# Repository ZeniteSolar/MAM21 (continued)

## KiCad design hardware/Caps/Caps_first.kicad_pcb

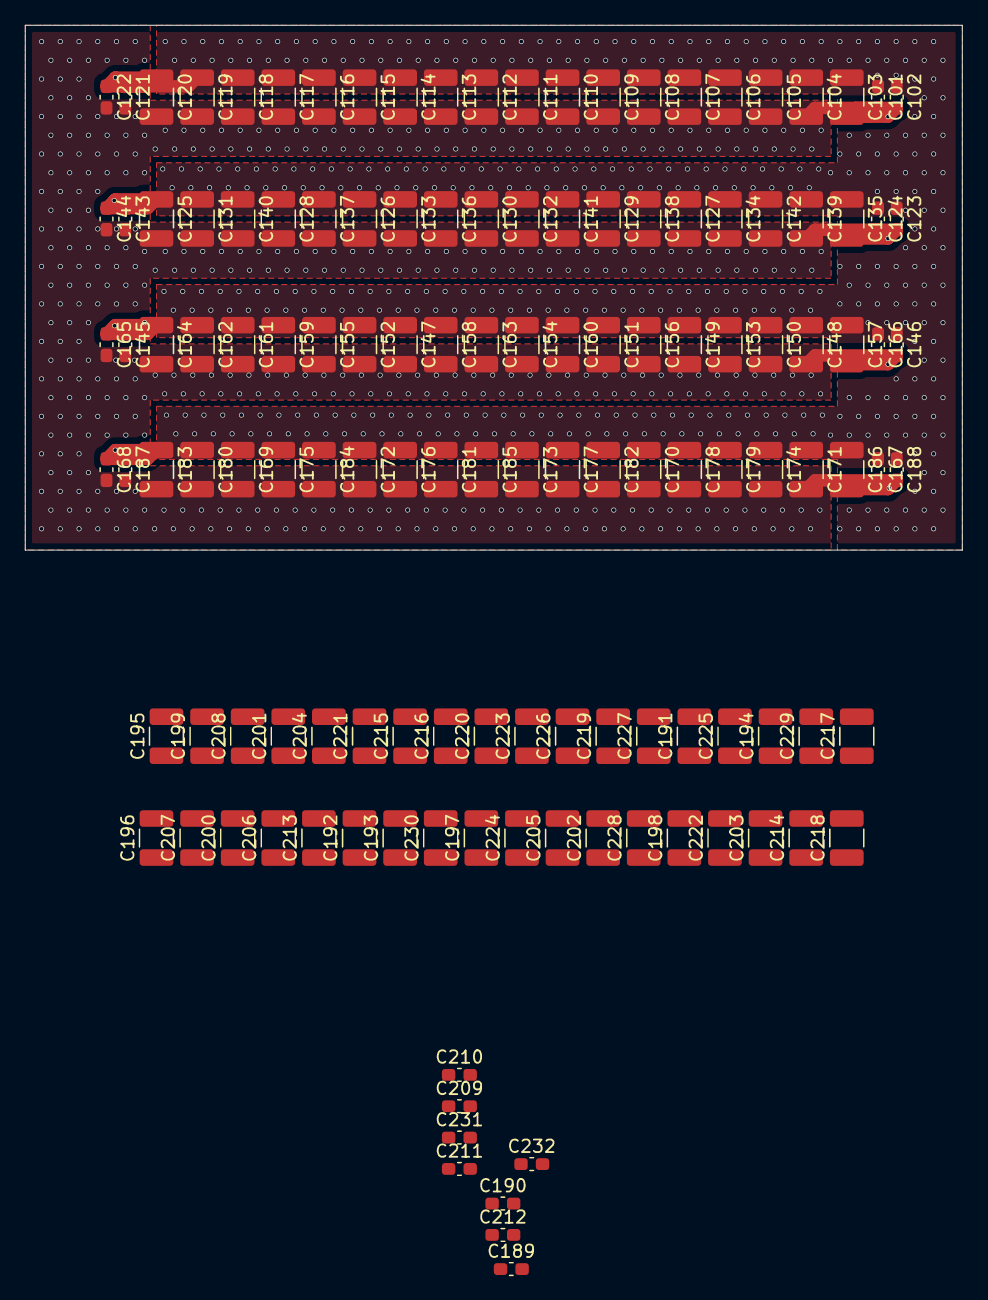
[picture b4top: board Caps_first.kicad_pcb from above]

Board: 2 copper layers, 75.0 x 42.0 mm, 132 parts (0 on the bottom side), 2 nets.

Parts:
C101, C102, C121, C122, C123, C124, C143, C144, C145, C146, C165, C166, C167, C168, C187, C188, C189, C190, C209, C210, C211, C212, C231, C232: 100n 100V X7; C_0603_1608Metric_Pad1.08x0.95mm_HandSolder
C103, C104, C105, C106, C107, C108, C109, C110, C111, C112, C113, C114, C115, C116, C117, C118, C119, C120, C125, C126, C127, C128, C129, C130, C131, C132, C133, C134, C135, C136, C137, C138, C139, C140, C141, C142, C147, C148, C149, C150, C151, C152, C153, C154, C155, C156, C157, C158, C159, C160, C161, C162, C163, C164, C169, C170, C171, C172, C173, C174, C175, C176, C177, C178, C179, C180, C181, C182, C183, C184, C185, C186, C191, C192, C193, C194, C195, C196, C197, C198, C199, C200, C201, C202, C203, C204, C205, C206, C207, C208, C213, C214, C215, C216, C217, C218, C219, C220, C221, C222, C223, C224, C225, C226, C227, C228, C229, C230: 4.7u 100V X7; C_1210_3225Metric_Pad1.33x2.70mm_HandSolder

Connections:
+BATT: C101.1, C102.1, C103.1, C104.1, C105.1, C106.1, C107.1, C108.1, C109.1, C110.1, C111.1, C112.1, C113.1, C114.1, C115.1, C116.1, C117.1, C118.1, C119.1, C120.1, C121.1, C122.1, C123.1, C124.1, C125.1, C126.1, C127.1, C128.1, C129.1, C130.1, C131.1, C132.1, C133.1, C134.1, C135.1, C136.1, C137.1, C138.1, C139.1, C140.1, C141.1, C142.1, C143.1, C144.1, C145.1, C146.1, C147.1, C148.1, C149.1, C150.1, C151.1, C152.1, C153.1, C154.1, C155.1, C156.1, C157.1, C158.1, C159.1, C160.1, C161.1, C162.1, C163.1, C164.1, C165.1, C166.1, C167.1, C168.1, C169.1, C170.1, C171.1, C172.1, C173.1, C174.1, C175.1, C176.1, C177.1, C178.1, C179.1, C180.1, C181.1, C182.1, C183.1, C184.1, C185.1, C186.1, C187.1, C188.1, C189.1, C190.1, C191.1, C192.1, C193.1, C194.1, C195.1, C196.1, C197.1, C198.1, C199.1, C200.1, C201.1, C202.1, C203.1, C204.1, C205.1, C206.1, C207.1, C208.1, C209.1, C210.1, C211.1, C212.1, C213.1, C214.1, C215.1, C216.1, C217.1, C218.1, C219.1, C220.1, C221.1, C222.1, C223.1, C224.1, C225.1, C226.1, C227.1, C228.1, C229.1, C230.1, C231.1, C232.1
-BATT: C101.2, C102.2, C103.2, C104.2, C105.2, C106.2, C107.2, C108.2, C109.2, C110.2, C111.2, C112.2, C113.2, C114.2, C115.2, C116.2, C117.2, C118.2, C119.2, C120.2, C121.2, C122.2, C123.2, C124.2, C125.2, C126.2, C127.2, C128.2, C129.2, C130.2, C131.2, C132.2, C133.2, C134.2, C135.2, C136.2, C137.2, C138.2, C139.2, C140.2, C141.2, C142.2, C143.2, C144.2, C145.2, C146.2, C147.2, C148.2, C149.2, C150.2, C151.2, C152.2, C153.2, C154.2, C155.2, C156.2, C157.2, C158.2, C159.2, C160.2, C161.2, C162.2, C163.2, C164.2, C165.2, C166.2, C167.2, C168.2, C169.2, C170.2, C171.2, C172.2, C173.2, C174.2, C175.2, C176.2, C177.2, C178.2, C179.2, C180.2, C181.2, C182.2, C183.2, C184.2, C185.2, C186.2, C187.2, C188.2, C189.2, C190.2, C191.2, C192.2, C193.2, C194.2, C195.2, C196.2, C197.2, C198.2, C199.2, C200.2, C201.2, C202.2, C203.2, C204.2, C205.2, C206.2, C207.2, C208.2, C209.2, C210.2, C211.2, C212.2, C213.2, C214.2, C215.2, C216.2, C217.2, C218.2, C219.2, C220.2, C221.2, C222.2, C223.2, C224.2, C225.2, C226.2, C227.2, C228.2, C229.2, C230.2, C231.2, C232.2

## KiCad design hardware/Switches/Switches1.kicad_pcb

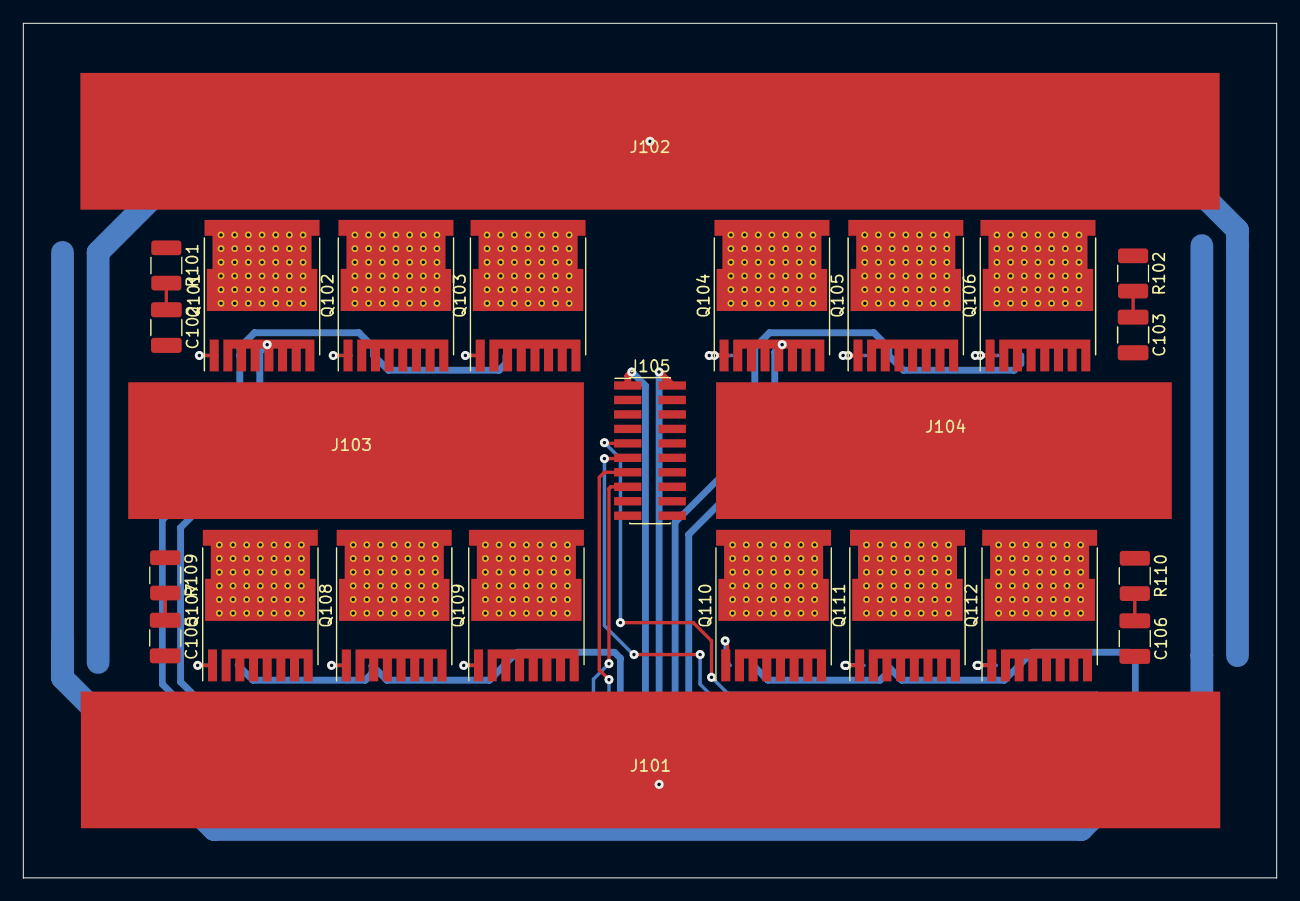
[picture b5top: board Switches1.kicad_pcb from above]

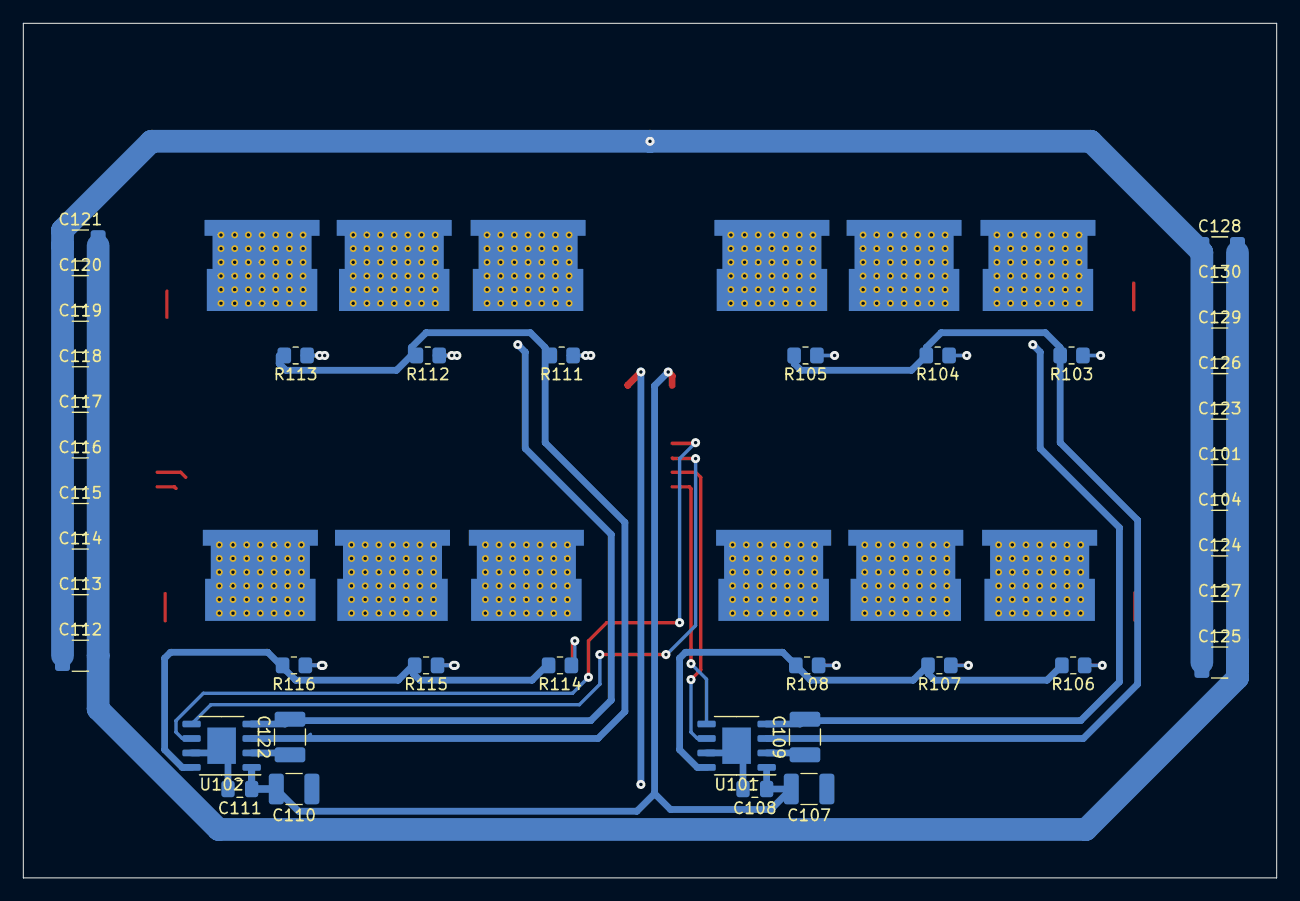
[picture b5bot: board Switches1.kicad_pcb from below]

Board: 2 copper layers, 110.0 x 75.0 mm, 65 parts (40 on the bottom side), 31 nets.

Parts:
C101, C104, C112, C113, C114, C115, C116, C117, C118, C119, C120, C121, C123, C124, C125, C126, C127, C128, C129, C130: 10u; C_1210_3225Metric_Pad1.33x2.70mm_HandSolder
C102, C103, C105, C106: 100n; C_1210_3225Metric_Pad1.33x2.70mm_HandSolder
C107, C109, C110, C122: 10uF; C_1210_3225Metric_Pad1.33x2.70mm_HandSolder
C108, C111: 100nF; C_0805_2012Metric_Pad1.18x1.45mm_HandSolder
J101, J102, J103, J104: BusBar
J105: Conn_02x03_Odd_Even; PinHeader_2x10_P1.27mm_Vertical_SMD
Q101, Q102, Q103, Q104, Q105, Q106, Q107, Q108, Q109, Q110, Q111, Q112: IPT015N10N5; Infineon_PG-HSOF-8-1_ThermalVias
R101, R102, R109, R110: 10; R_1210_3225Metric_Pad1.30x2.65mm_HandSolder
R103, R104, R105, R106, R107, R108, R111, R112, R113, R114, R115, R116: 4R7; R_0805_2012Metric_Pad1.20x1.40mm_HandSolder
U101, U102: UCC27211DDAR; SOIC-8-1EP_3.9x4.9mm_P1.27mm_EP2.514x3.2mm

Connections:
+15V: C107.2, C108.1, C110.2, C111.1, J105.1, U101.1, U102.1
/GH1_1: Q101.1, R103.1
/GH1_2: Q102.1, R104.1
/GH1_3: Q103.1, R105.1
/GH2_1: Q104.1, R111.1
/GH2_2: Q105.1, R112.1
/GH2_3: Q106.1, R113.1
/GL1_1: Q107.1, R106.1
/GL1_2: Q108.1, R107.1
/GL1_3: Q109.1, R108.1
/GL2_1: Q110.1, R114.1
/GL2_2: Q111.1, R115.1
/GL3_3: Q112.1, R116.1
/PWM_H1: J105.15, U101.5
/PWM_H2: J105.11, U102.5
/PWM_L1: J105.13, U101.6
/PWM_L2: J105.9, U102.6
/SL1: C102.2, C109.2, J103.1, Q101.2, Q102.2, Q103.2, Q107.3, Q108.3, Q109.3, R109.1, U101.4
/SL2: C103.2, C122.2, J104.1, Q104.2, Q105.2, Q106.2, Q110.3, Q111.3, Q112.3, R110.1, U102.4
/Vin: C101.1, C104.1, C112.1, C113.1, C114.1, C115.1, C116.1, C117.1, C118.1, C119.1, C120.1, C121.1, C123.1, C124.1, C125.1, C126.1, C127.1, C128.1, C129.1, C130.1, J102.1, Q101.3, Q102.3, Q103.3, Q104.3, Q105.3, Q106.3, R101.1, R102.1
GND: C101.2, C104.2, C105.2, C106.2, C107.1, C108.2, C110.1, C111.2, C112.2, C113.2, C114.2, C115.2, C116.2, C117.2, C118.2, C119.2, C120.2, C121.2, C123.2, C124.2, C125.2, C126.2, C127.2, C128.2, C129.2, C130.2, J101.1, J105.2, Q107.2, Q108.2, Q109.2, Q110.2, Q111.2, Q112.2, U101.7, U101.9, U102.7, U102.9
unnamed: C102.1, R101.2
unnamed: C103.1, R102.2
unnamed: C105.1, R109.2
unnamed: C106.1, R110.2
unnamed: C109.1, U101.2
unnamed: C122.1, U102.2
unnamed: R103.2, R104.2, R105.2, U101.3
unnamed: R106.2, R107.2, R108.2, U101.8
unnamed: R111.2, R112.2, R113.2, U102.3
unnamed: R114.2, R115.2, R116.2, U102.8

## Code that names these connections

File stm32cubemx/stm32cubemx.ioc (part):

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Mcu.Name=STM32F103C(8-B)Tx
Mcu.Package=LQFP48
Mcu.UserName=STM32F103C8Tx
PA0-WKUP.Signal=ADCx_IN0
PA1.Signal=ADCx_IN1
PA11.Mode=CAN_Activate
PA11.Signal=CAN_RX
PA12.Mode=CAN_Activate
PA12.Signal=CAN_TX
PA13.Mode=Serial_Wire
PA13.Signal=SYS_JTMS-SWDIO
PA14.Mode=Serial_Wire
PA14.Signal=SYS_JTCK-SWCLK
PA2.Signal=ADCx_IN2
PA3.Signal=ADCx_IN3
PA4.Signal=ADCx_IN4
PA5.Signal=ADCx_IN5
PA6.GPIOParameters=GPIO_Label
PA6.GPIO_Label=FAN
PA6.Signal=S_TIM3_CH1
PA8.Signal=S_TIM1_CH1
PA9.Signal=S_TIM1_CH2
PB0.GPIOParameters=GPIO_Label
PB0.GPIO_Label=LED0
PB0.Signal=GPIO_Output
PB1.GPIOParameters=GPIO_Label
PB1.GPIO_Label=LED1
PB1.Signal=GPIO_Output
PB10.Mode=Asynchronous
PB10.Signal=USART3_TX
PB11.Mode=Asynchronous
PB11.Signal=USART3_RX
PB13.Mode=PWM Generation1 CH1 CH1N
PB13.Signal=TIM1_CH1N
PB14.Mode=PWM Generation2 CH2 CH2N
PB14.Signal=TIM1_CH2N
PD0-OSC_IN.Mode=HSE-External-Oscillator
PD0-OSC_IN.Signal=RCC_OSC_IN
PD1-OSC_OUT.Mode=HSE-External-Oscillator
PD1-OSC_OUT.Signal=RCC_OSC_OUT
RCC.SYSCLKFreq_VALUE=16000000
RCC.SYSCLKSource=RCC_SYSCLKSOURCE_PLLCLK
board=custom

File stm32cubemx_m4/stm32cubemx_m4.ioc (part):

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Mcu.Name=STM32G431C(6-8-B)Tx
Mcu.Package=LQFP48
Mcu.UserName=STM32G431C8Tx
PA0.Mode=IN1-Differential
PA0.Signal=ADC1_IN1
PA1.Mode=IN1-Differential
PA1.Signal=ADC1_IN2
PA11.Mode=FDCAN_Activate
PA11.Signal=FDCAN1_RX
PA12.Mode=FDCAN_Activate
PA12.Signal=FDCAN1_TX
PA13.Mode=Trace_Asynchronous_SW
PA13.Signal=SYS_JTMS-SWDIO
PA14.Mode=Trace_Asynchronous_SW
PA14.Signal=SYS_JTCK-SWCLK
PA15.GPIOParameters=GPIO_Label
PA15.GPIO_Label=FAN
PA15.Signal=S_TIM2_CH1
PA2.Mode=IN3-Differential
PA2.Signal=ADC1_IN3
PA3.Mode=IN3-Differential
PA3.Signal=ADC1_IN4
PA6.Mode=IN3-Differential
PA6.Signal=ADC2_IN3
PA7.Mode=IN3-Differential
PA7.Signal=ADC2_IN4
PA8.Signal=S_TIM1_CH1
PA9.Signal=S_TIM1_CH2
PB13.Mode=Output Compare1 CH1 CH1N
PB13.Signal=TIM1_CH1N
PB14.Mode=Output Compare2 CH2 CH2N
PB14.Signal=TIM1_CH2N
PB3.Mode=Trace_Asynchronous_SW
PB3.Signal=SYS_JTDO-SWO
PB4.GPIOParameters=GPIO_Label
PB4.GPIO_Label=LED0
PB4.Signal=GPIO_Output
PB5.GPIOParameters=GPIO_Label
PB5.GPIO_Label=LED1
PB5.Signal=GPIO_Output
PB6.Mode=Asynchronous
PB6.Signal=USART1_TX
PB7.Mode=Asynchronous
PB7.Signal=USART1_RX
PB8-BOOT0.GPIOParameters=GPIO_Label
PB8-BOOT0.GPIO_Label=BOOT0
PB8-BOOT0.Signal=GPIO_Input
PF0-OSC_IN.Mode=HSE-External-Oscillator
PF0-OSC_IN.Signal=RCC_OSC_IN
PF1-OSC_OUT.Mode=HSE-External-Oscillator
PF1-OSC_OUT.Signal=RCC_OSC_OUT
PG10-NRST.GPIOParameters=GPIO_Label
PG10-NRST.GPIO_Label=FREQ_DEBUG
PG10-NRST.Mode=Clock-out
PG10-NRST.Signal=RCC_MCO
RCC.HSE_VALUE=8000000
RCC.SYSCLKFreq_VALUE=170000000
RCC.SYSCLKSource=RCC_SYSCLKSOURCE_PLLCLK
board=custom

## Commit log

2020-09-09 Add an initial version of the system diagram
2020-09-09 Add a markdown file to show the diagrams
2020-09-11 SVG exported
2020-09-11 Use .svg instead of .png
2020-09-11 Diagrama Geral (#4)
    * Add an initial version of the system diagram
    * Add a markdown file to show the diagrams
    * SVG exported
    * Use .svg instead of .png
2020-09-19 topology diagram added
2020-09-30 topology diagram added (#5)
2020-10-03 basic documentation
2020-10-03 documentation updated
2020-10-03 moved all diagrams to diagrams's folder
2020-10-06 Implement simple 4 quadrant test case using the Pilot Controller
2020-10-06 Código e simulação de teste do ADC adicionados
2020-10-06 Firmware cleanup and basic setup with the following tests:
    - ADC_CLOCK and MACHINE_CLOCK signals: ok
    - ADC_CLOCK frequency is correct: ???
    - MACHINE_CLOCK frequency is correct: ???
    - ADC reading values and calibrated: ok
    - Filters and gain are working: ok
    - Enable, Regen, Rev, Power signals: ok
2020-10-06 Documentação inicial adicionada
2020-10-06 Add the digital embedded controller and more
    - Discrete PWM Controller added: not in use, just for reference.
    - Embedded Controller added, with the code from MCB19
    - Ideal Voltage and Current sensors added for both Input and Output.
    - Signal Conditioning added, with ideal filters and gains.
    - PWM Peripheral added, using SAR topology, containing delay between
    channels, a common clock feeding a sample/hold.
2020-10-06 Add script to test the equation of the PWM controller
2020-10-06 Simulation with mosfet logic working
2020-10-06 Better formating + TOC
2020-10-06 Add anchor links to TOC
2020-10-06 Fix wrong img
2020-10-08 Ideal simulation (#10)
    * Simulation with mosfet logic working
    * Add the digital embedded controller and more
    - Discrete PWM Controller added: not in use, just for reference.
    - Embedded Controller added, with the code from MCB19
    - Ideal Voltage and Current sensors added for both Input and Output.
    - Signal Conditioning added, with ideal filters and gains.
2020-10-08 Documentation (#9)
    * basic documentation
    * moved all diagrams to diagrams' folder
2020-10-29 ME0909 modelling data and scripts added
2020-10-29 Add datasheet and its extracted data
2020-10-29 Add images from motor teardown
2020-10-29 Add markdown file to show the images
2020-10-29 Plots and prints fixed
2021-01-02 Add data extracted from Performance Data using WebPlotDigitizer
2021-03-09 starting Mosfet PCB
2021-03-09 snubber
2021-04-02 Initial stm32cubemx project
2021-04-02 placa de controle
2021-04-03 adicionado o TL7726 e modificada a placa
2021-04-04 wip: switches pcb routed
2021-04-05 Driver and MOSFETs protections added, driver calculations done.
2021-04-08 wip: PCB updated
2021-04-08 control PCB updated
2021-04-09 Added Cortex M4 possibility
2021-04-09 Updating Switches PCB
2021-04-09 Adding crystal output pin for freq debug
2021-04-09 Update Controle PCB
2021-04-09 Crystal removed, FAN and LEDs pins changed.
2021-04-10 first version of layout
2021-04-10 falta acabamento
2021-04-11 Controle PCB waiting revision
2021-04-12 Add capacitor PCB
2021-04-12 Add simulation files
2021-04-12 PCB updated, not yet finished
2021-04-12 vias
2021-04-12 more vias!
2021-04-12 Done, not yet checked
2021-04-12 A lot of clarance issues fixed
2021-04-12 Changed to 4 layers because the need of tg-150 material. Gerbers added.
2021-04-12 wip controle holes
2021-04-12 A lot of clarance issues fixed, gerbers added
2021-04-12 Gerbers re-exported
2021-04-12 dimensions and holes modified
2021-04-12 export files
2021-04-12 PCB updated with holes
2021-04-12 Remove smd references and values from silkscreen.
2021-04-12 Add Kicad 3D stack.
2021-04-12 dimensions reduced
2021-04-12 controle GERBER
2021-04-12 basic 3D positioning done.
2021-04-12 wip 3D
2021-04-12 Zip gerbers for Controle PCB
2021-04-12 silkscreen and export gerbers
2021-04-12 small changes (compnents values)
2021-04-12 Gerbers re-generated with JCLJCLJLC.. string
2021-04-12 Add more holes to better pull the heatsink
2021-04-12 Remove the solder mask from heatsink region
2021-04-12 3D updated, copper bars added with holes
2021-04-12 Gerbers updated
2021-04-28 Add mechanical files
2021-04-28 Updated PCB for fabrication
2021-04-28 Update from last development cycle
2021-04-28 Update busbar size and reassembly the parts together
2022-06-18 Transmit and receve CAN messages
2022-06-18 configure TIMER1 and PWMs
2022-06-18 add STM32 Cube gitignore
2022-06-18 remove generated and temporary files
2022-06-19 firmware: Hello World!
2022-06-19 cargo: Fix project dependencies.
2022-06-19 cargo: Use the right target for cortex-m4, add qemu option.
2022-06-19 src: PWM and CAN configured.
2022-06-19 src: Add leds.
2022-07-04 add interesant images
2022-07-04 add sign-magnitude drive modulation with thermal stabilization
2022-07-18 Switch to stm32_hal2, configure PWM.
2022-07-19 add an inefficient way to turn off PWM in the initial state and when boat off message is received, this code need to be refactored
2022-07-19 remove eclipse and vscode files
2022-07-31 WIP: headers for the state machine
2022-07-31 WIP: canbus aplication
2022-07-31 WIP: motor controller headers
2022-08-01 WIP working in the logic of the control machine state
2022-08-02 add states for the control and h_bridge state machine
2022-08-02 CAN: implement message extractor
2022-08-03 MACHINE: privatize machine struct
2022-08-03 FIX: add missing break in control state machine
2022-08-03 CONTROL: fix pwm control action
2022-08-03 Ignore build folder.
2022-08-03 Add compiler flags to help with better code quality.
2022-08-05 WIP: tryng to use trice logger
2022-08-05 Format code
2022-08-05 gitignore: add useless kicad and ltspice files
2022-08-05 Documentation: Add some information about control and machine functions
2022-08-05 Some internal functions converted to static ones to increase security
2022-08-05 control: fixed error that ignore control action when control error was negative, due to bad control error calculation
2022-08-05 Documentation: Add some information about H bridge
2022-08-05 h_bridge: guarantees that the switches initialize turned off
2022-08-05 h_bridge: invert duty cycle if channel is in pwm mode 2
2022-08-05 Documentation: Add more information about h bridge functions
2022-08-05 h_bridge: remove testing pin
2022-08-05 h_bridge: Some internal functions converted to static ones to increase security
2022-08-08 WIP canbus
2022-08-16 Update comments
2022-08-16 Add can hardware configuration
2022-08-16 control: Improve soft pwm
2022-08-16 h_bridge: change pwm limits
2022-08-16 h_bridge: fix that pwm was inverted in reverse state
2022-08-16 remove dos characters in makefile
2022-08-17 use the CAN_PARSER lib to parse can messages
2022-08-25 add calculus of snubber, and calculate first iteration
2022-08-25 calculate power loss
2022-08-25 calculate low side snubber
2022-08-29 measure resonant frequency of high side again because last measurement was without capacitor bank
2022-08-29 update kicad files to kicad 6
2022-08-29 WIP: modeling motor in LTspice
2022-08-29 CAN: specify can fifo in config
2022-08-29 CAN: fixed some float variables casting to int and some conversions to float
2022-08-29 set real frequency in the parser
2022-08-29 control: improve duty cycle computation constants and fix bug that in small steps the duty cycle smooth algorithm didnt work
2022-08-29 machine: improve some constants and fix identation
2022-08-29 main: small optimization in the timer interruption
2022-08-29 control: add control machine state diagram
2022-08-29 remove temporarily file
2022-09-02 snubber: plot tests data
2022-09-05 add new test with differents tecnologies of capacitors
2022-09-05 run jupyter cells
2022-09-05 Add python virtualenv setup.
2022-09-10 add test with differents capacitors technologies
2023-02-16 Upload images of the board
